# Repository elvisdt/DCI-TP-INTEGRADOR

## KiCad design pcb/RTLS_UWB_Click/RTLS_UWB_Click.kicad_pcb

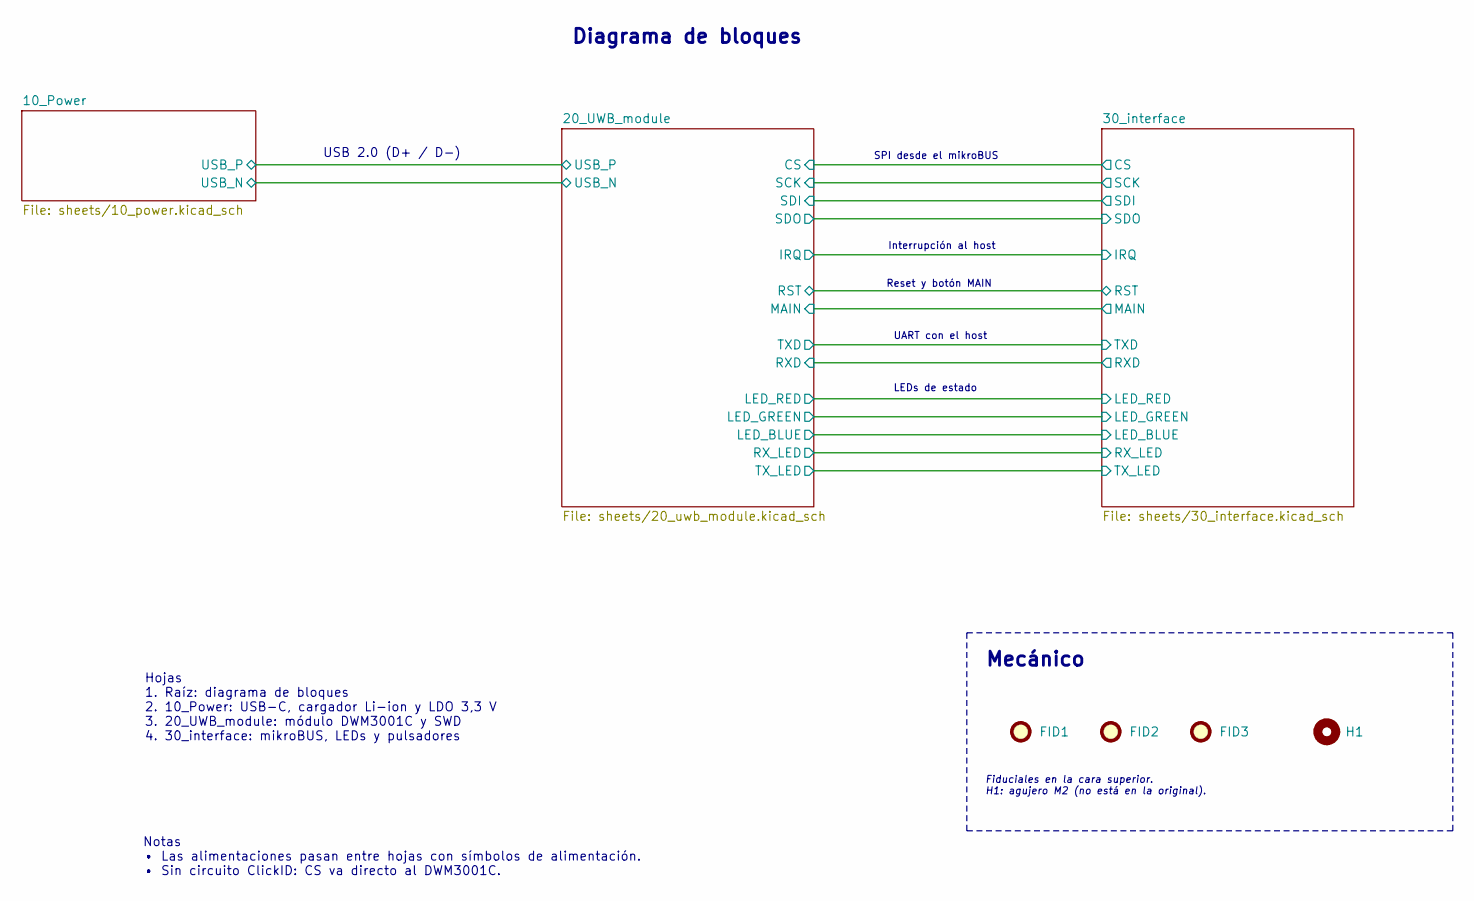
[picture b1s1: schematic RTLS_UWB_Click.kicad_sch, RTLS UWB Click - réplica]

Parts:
FID1, FID2, FID3: Fiducial; Fiducial_1mm_Mask2mm
H1: MountingHole; MountingHole_2.2mm_M2

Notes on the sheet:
UART con el host
Notas • Las alimentaciones pasan entre hojas con símbolos de alimentación. • Sin circuito ClickID: CS va directo al DWM3001C.
Reset y botón MAIN
LEDs de estado
SPI desde el mikroBUS
Interrupción al host
USB 2.0 (D+ / D−)
Fiduciales en la cara superior. H1: agujero M2 (no está en la original).
Hojas 1. Raíz: diagrama de bloques 2. 10_Power: USB-C, cargador Li-ion y LDO 3,3 V 3. 20_UWB_module: módulo DWM3001C y SWD 4. 30_interface: mikroBUS, LEDs y pulsadores
Mecánico
Diagrama de bloques

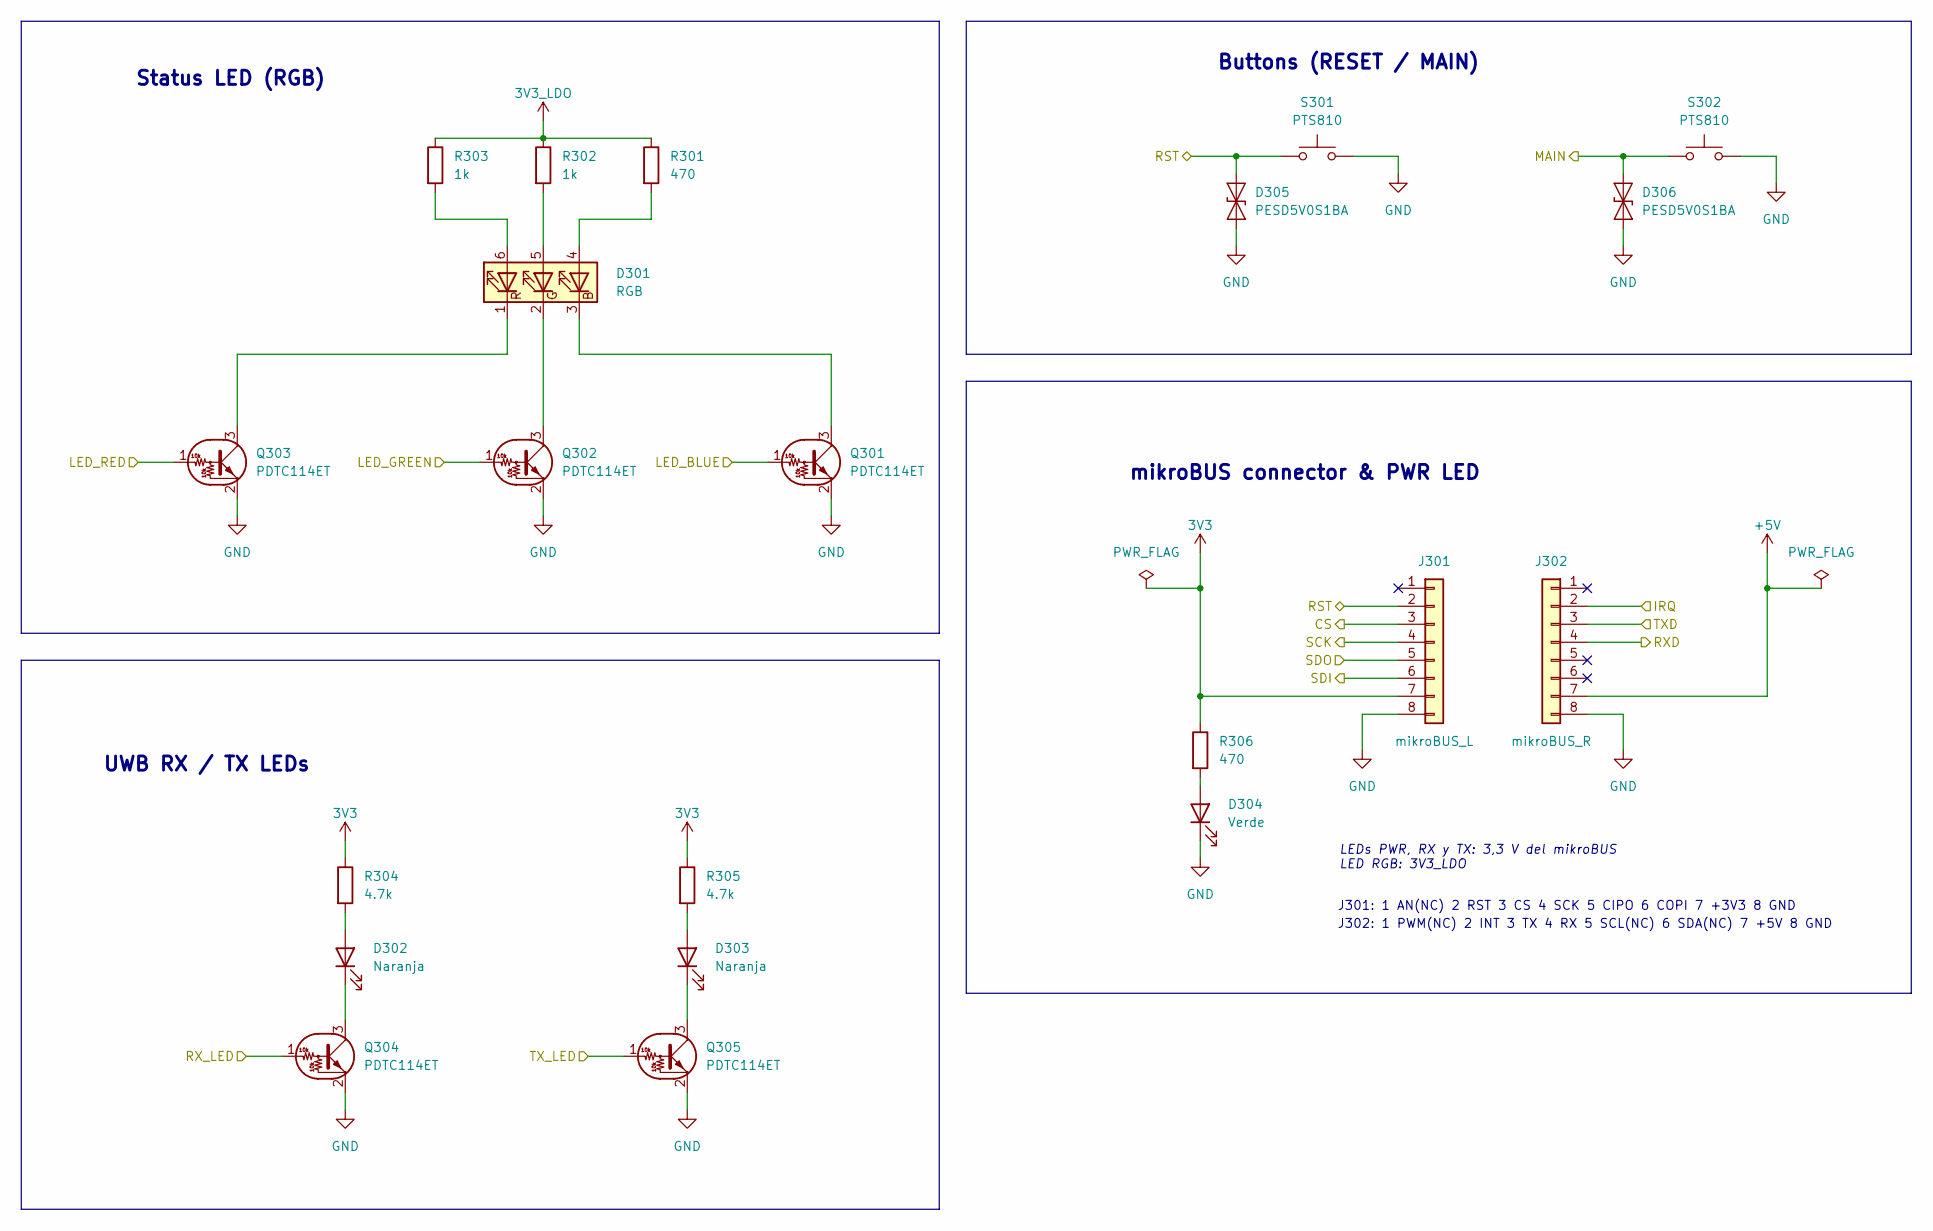
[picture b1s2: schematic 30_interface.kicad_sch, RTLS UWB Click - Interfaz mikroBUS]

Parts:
D301: RGB; LED_RGB_PLCC-6; Digikey# 516-3132-1-ND
D302, D303: Naranja; LED_0805_2012Metric; Digikey# 160-1425-1-ND
D304: Verde; LED_0805_2012Metric; Digikey# 160-1426-1-ND
D305, D306: PESD5V0S1BA; D_SOD-323; Digikey# 1727-PESD5V0S1BA,115CT-ND
J301: mikroBUS_L; PinHeader_1x08_P2.54mm_Vertical; Digikey# 732-5321-ND
J302: mikroBUS_R; PinHeader_1x08_P2.54mm_Vertical; Digikey# 732-5321-ND
Q301, Q302, Q303, Q304, Q305: PDTC114ET; SOT-23; Digikey# 1727-5131-1-ND
R301, R306: 470; R_0805_2012Metric; Digikey# 311-470CRCT-ND
R302, R303: 1k; R_0805_2012Metric; Digikey# 311-1.00KCRCT-ND
R304, R305: 4.7k; R_0805_2012Metric; Digikey# 311-4.70KCRCT-ND
S301, S302: PTS810; SW_SPST_PTS810; Digikey# CKN10504CT-ND

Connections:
3V3: J301.7, R304.1, R305.1, R306.1
3V3_LDO: R301.1, R302.1, R303.1; also elsewhere on the board
+5V: J302.7; also elsewhere on the board
/20_UWB_module/CS: J301.3; also elsewhere on the board
/20_UWB_module/IRQ: J302.2; also elsewhere on the board
/20_UWB_module/LED_BLUE: Q301.1 (B); also elsewhere on the board
/20_UWB_module/LED_GREEN: Q302.1 (B); also elsewhere on the board
/20_UWB_module/LED_RED: Q303.1 (B); also elsewhere on the board
/20_UWB_module/MAIN: D306.2 (A2), S302.1; also elsewhere on the board
/20_UWB_module/RST: D305.2 (A2), J301.2, S301.1; also elsewhere on the board
/20_UWB_module/RXD: J302.4; also elsewhere on the board
/20_UWB_module/RX_LED: Q304.1 (B); also elsewhere on the board
/20_UWB_module/SCK: J301.4; also elsewhere on the board
/20_UWB_module/SDI: J301.6; also elsewhere on the board
/20_UWB_module/SDO: J301.5; also elsewhere on the board
/20_UWB_module/TXD: J302.3; also elsewhere on the board
/20_UWB_module/TX_LED: Q305.1 (B); also elsewhere on the board
GND: D304.1 (K), D305.1 (A1), D306.1 (A1), J301.8, J302.8, Q301.2 (E), Q302.2 (E), Q303.2 (E), Q304.2 (E), Q305.2 (E), S301.2, S302.2; also elsewhere on the board
unnamed: D301.4 (BA), R301.2
unnamed: D301.3 (BK), Q301.3 (C)
unnamed: D301.5 (GA), R302.2
unnamed: D301.2 (GK), Q302.3 (C)
unnamed: D301.6 (RA), R303.2
unnamed: D301.1 (RK), Q303.3 (C)
unnamed: D302.2 (A), R304.2
unnamed: D302.1 (K), Q304.3 (C)
unnamed: D303.2 (A), R305.2
unnamed: D303.1 (K), Q305.3 (C)
unnamed: D304.2 (A), R306.2

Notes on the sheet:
J301: 1 AN(NC) 2 RST 3 CS 4 SCK 5 CIPO 6 COPI 7 +3V3 8 GND
mikroBUS connector & PWR LED
J302: 1 PWM(NC) 2 INT 3 TX 4 RX 5 SCL(NC) 6 SDA(NC) 7 +5V 8 GND
Buttons (RESET / MAIN)
UWB RX / TX LEDs
LEDs PWR, RX y TX: 3,3 V del mikroBUS LED RGB: 3V3_LDO
Status LED (RGB)

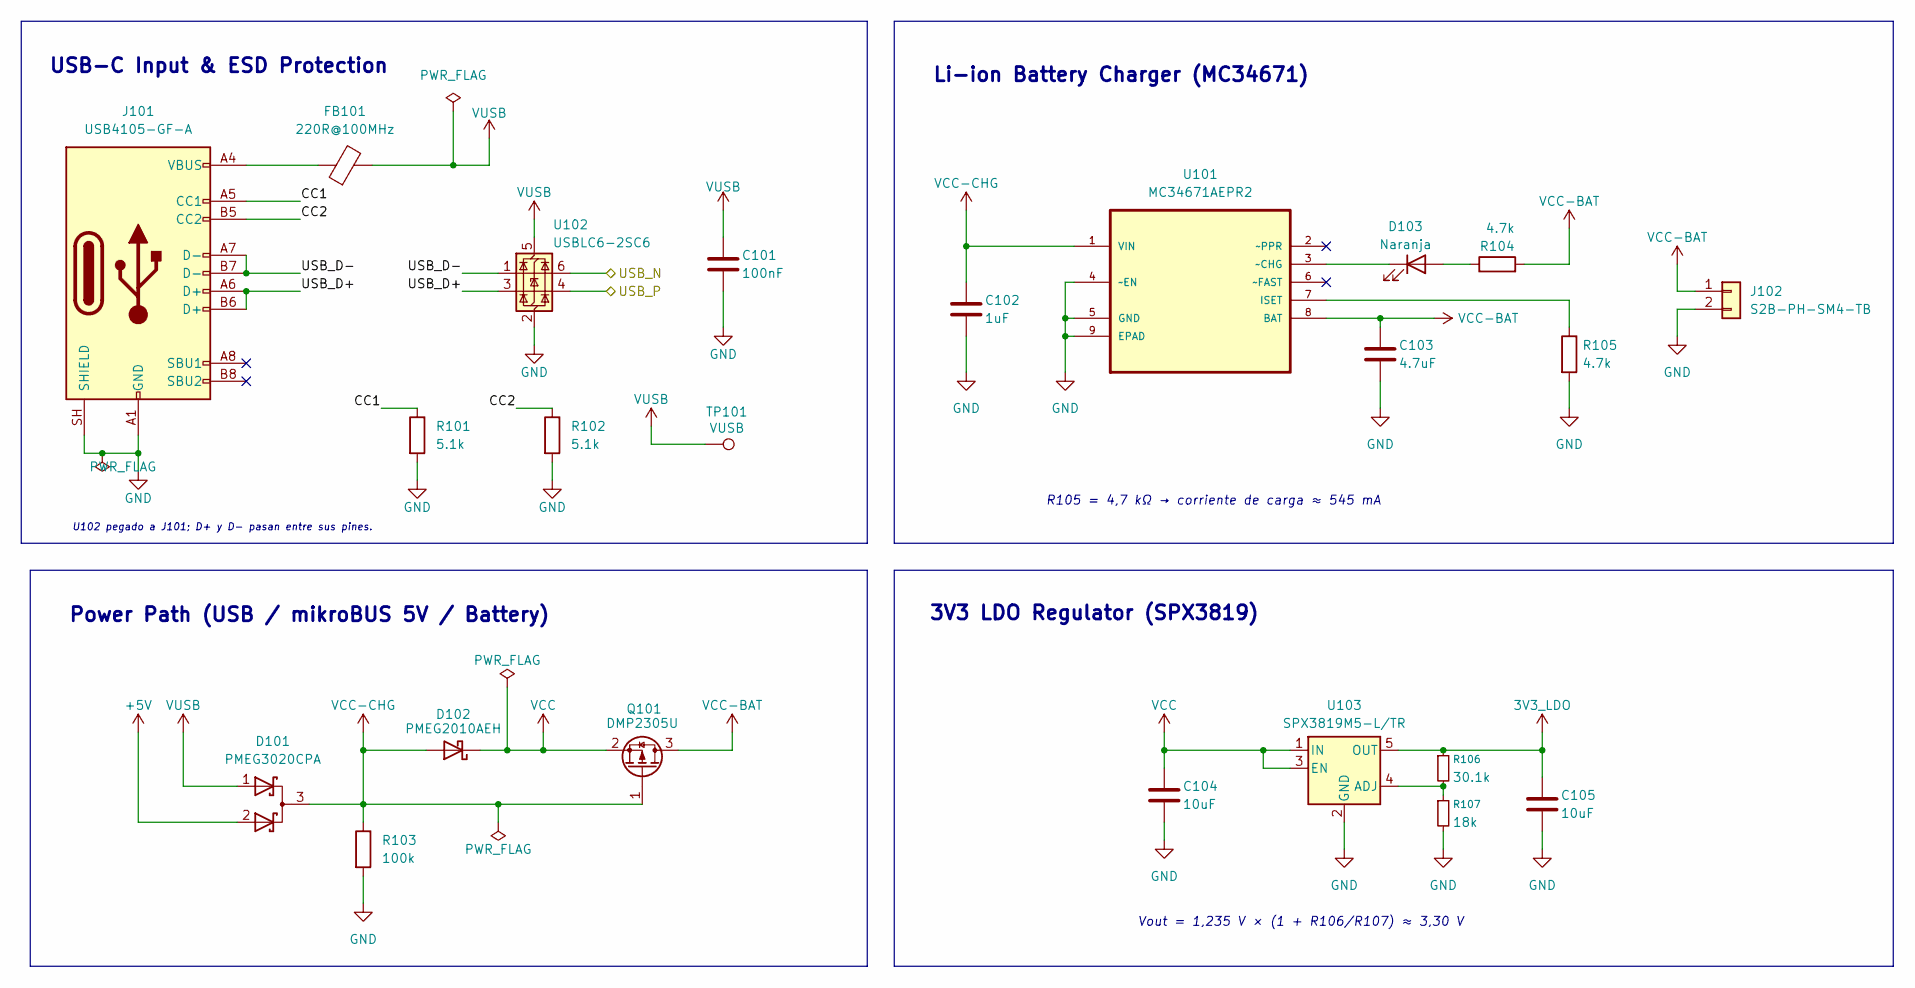
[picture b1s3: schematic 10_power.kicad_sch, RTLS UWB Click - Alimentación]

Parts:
C101: 100nF; C_0805_2012Metric; Digikey# 1276-1003-1-ND
C102: 1uF; C_0805_2012Metric; Digikey# 1276-1066-1-ND
C103: 4.7uF; C_0805_2012Metric; Digikey# 1276-1244-1-ND
C104, C105: 10uF; C_0805_2012Metric; Digikey# 1276-2891-1-ND
D101: PMEG3020CPA; HUSON-3-1EP_2x2mm_P1.3mm_EP1.1x1.6mm; Digikey# 1727-5205-1-ND
D102: PMEG2010AEH; D_SOD-123F; Digikey# 1727-3856-1-ND
D103: Naranja; LED_0805_2012Metric; Digikey# 160-1425-1-ND
FB101: 220R@100MHz; L_0805_2012Metric; Digikey# 490-1054-1-ND
J101: USB4105-GF-A; USB_C_Receptacle_GCT_USB4105-xx-A_16P_TopMnt_Horizontal; Digikey# 2073-USB4105-GF-ACT-ND
J102: S2B-PH-SM4-TB; JST_PH_S2B-PH-SM4-TB_1x02-1MP_P2.00mm_Horizontal; Digikey# 455-S2B-PH-SM4-TBCT-ND
Q101: DMP2305U; SOT-23; Digikey# DMP2305UDICT-ND
R101, R102: 5.1k; R_0805_2012Metric; Digikey# 311-5.10KCRCT-ND
R103: 100k; R_0805_2012Metric; Digikey# 311-100KCRCT-ND
R104, R105: 4.7k; R_0805_2012Metric; Digikey# 311-4.70KCRCT-ND
R106: 30.1k; R_0805_2012Metric; Digikey# 311-30.1KCRCT-ND
R107: 18k; R_0805_2012Metric; Digikey# 311-18.0KCRCT-ND
TP101: VUSB; TestPoint_Pad_D1.5mm
U101: MC34671AEPR2; DFN200X300X65-9N; Digikey# MC34671AEPR2CT-ND
U102: USBLC6-2SC6; SOT-23-6; Digikey# 497-5235-1-ND
U103: SPX3819M5-L/TR; SOT-23-5; Digikey# 1016-1871-1-ND

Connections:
3V3_LDO: C105.1, R106.1, U103.5 (OUT); also elsewhere on the board
+5V: D101.2 (A); also elsewhere on the board
/10_Power/CC1: J101.A5 (CC1), R101.1
/10_Power/CC2: J101.B5 (CC2), R102.1
/10_Power/USB_D+: J101.A6 (D+), J101.B6 (D+), U102.3 (I/O2)
/10_Power/USB_D-: J101.A7 (D-), J101.B7 (D-), U102.1 (I/O1)
/10_Power/USB_N: U102.6 (I/O1); also elsewhere on the board
/10_Power/USB_P: U102.4 (I/O2); also elsewhere on the board
GND: C101.2, C102.2, C103.2, C104.2, C105.2, J101.A1 (GND), J101.A12 (GND), J101.B1 (GND), J101.B12 (GND), J101.SH (SHIELD), J102.2, R101.2, R102.2, R103.2, R105.2, R107.2, U101.4 (~EN), U101.5 (GND), U101.9 (EPAD), U102.2 (GND), U103.2 (GND); also elsewhere on the board
unnamed: D103.2 (A), R104.1
unnamed: D103.1 (K), U101.3 (~CHG)
unnamed: FB101.1, J101.A4 (VBUS), J101.A9 (VBUS), J101.B4 (VBUS), J101.B9 (VBUS)
unnamed: R105.1, U101.7 (ISET)
unnamed: R106.2, R107.1, U103.4 (ADJ)
VCC: C104.1, D102.1 (K), Q101.2 (S), U103.1 (IN), U103.3 (EN)
VCC-BAT: C103.1, J102.1, Q101.3 (D), R104.2, U101.8 (BAT)
VCC-CHG: C102.1, D101.3 (K), D102.2 (A), Q101.1 (G), R103.1, U101.1 (VIN)
VUSB: C101.1, D101.1 (A), FB101.2, TP101.1 (1_1), U102.5 (VBUS); also elsewhere on the board

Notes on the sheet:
Vout = 1,235 V × (1 + R106/R107) ≈ 3,30 V
3V3 LDO Regulator (SPX3819)
U102 pegado a J101; D+ y D− pasan entre sus pines.
USB-C Input & ESD Protection
R105 = 4,7 kΩ → corriente de carga ≈ 545 mA
Power Path (USB / mikroBUS 5V / Battery)
Li-ion Battery Charger (MC34671)

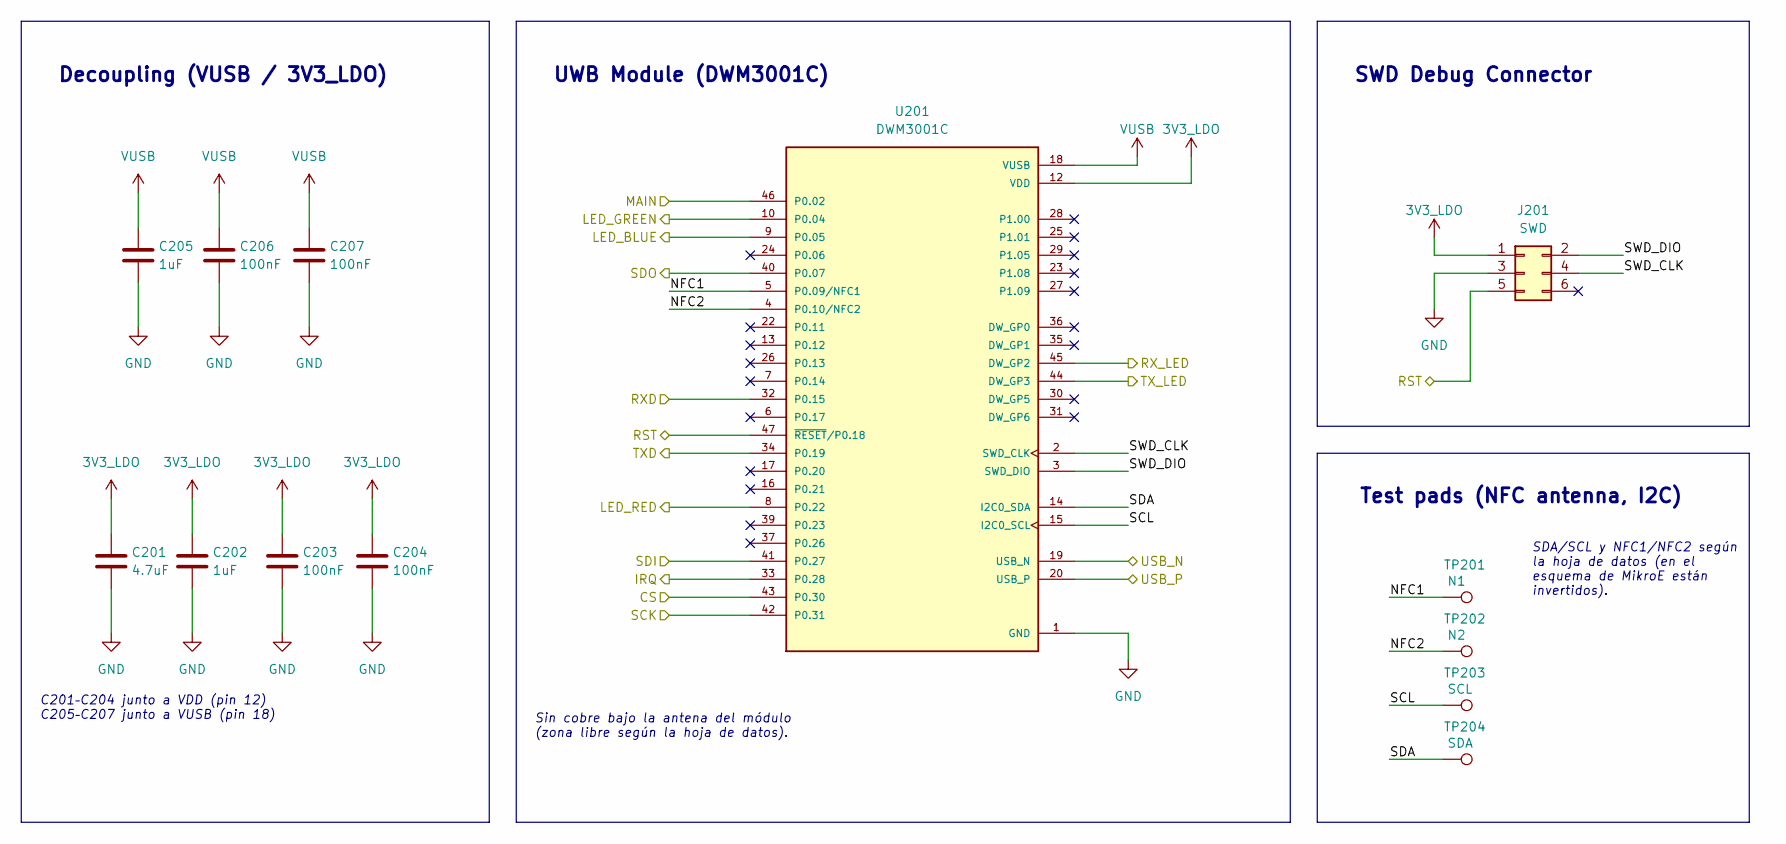
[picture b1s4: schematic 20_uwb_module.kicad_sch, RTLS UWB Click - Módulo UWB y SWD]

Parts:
C201: 4.7uF; C_0805_2012Metric; Digikey# 1276-1244-1-ND
C202, C205: 1uF; C_0805_2012Metric; Digikey# 1276-1066-1-ND
C203, C204, C206, C207: 100nF; C_0805_2012Metric; Digikey# 1276-1003-1-ND
J201: SWD; PinHeader_2x03_P1.27mm_Vertical; Digikey# SAM11230-ND
TP201: N1; TestPoint_Pad_D1.5mm
TP202: N2; TestPoint_Pad_D1.5mm
TP203: SCL; TestPoint_Pad_D1.5mm
TP204: SDA; TestPoint_Pad_D1.5mm
U201: DWM3001C; XCVR_DWM3001C; Digikey# 2312-DWM3001CTR13CT-ND

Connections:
3V3_LDO: C201.1, C202.1, C203.1, C204.1, J201.1, U201.12 (VDD); also elsewhere on the board
/10_Power/USB_N: U201.19 (USB_N); also elsewhere on the board
/10_Power/USB_P: U201.20 (USB_P); also elsewhere on the board
/20_UWB_module/CS: U201.43 (P0.30); also elsewhere on the board
/20_UWB_module/IRQ: U201.33 (P0.28); also elsewhere on the board
/20_UWB_module/LED_BLUE: U201.9 (P0.05); also elsewhere on the board
/20_UWB_module/LED_GREEN: U201.10 (P0.04); also elsewhere on the board
/20_UWB_module/LED_RED: U201.8 (P0.22); also elsewhere on the board
/20_UWB_module/MAIN: U201.46 (P0.02); also elsewhere on the board
/20_UWB_module/NFC1: TP201.1 (1_1), U201.5 (P0.09/NFC1)
/20_UWB_module/NFC2: TP202.1 (1_1), U201.4 (P0.10/NFC2)
/20_UWB_module/RST: J201.5, U201.47 (~RESET/P0.18); also elsewhere on the board
/20_UWB_module/RXD: U201.32 (P0.15); also elsewhere on the board
/20_UWB_module/RX_LED: U201.45 (DW_GP2); also elsewhere on the board
/20_UWB_module/SCK: U201.42 (P0.31); also elsewhere on the board
/20_UWB_module/SCL: TP203.1 (1_1), U201.15 (I2C0_SCL)
/20_UWB_module/SDA: TP204.1 (1_1), U201.14 (I2C0_SDA)
/20_UWB_module/SDI: U201.41 (P0.27); also elsewhere on the board
/20_UWB_module/SDO: U201.40 (P0.07); also elsewhere on the board
/20_UWB_module/SWD_CLK: J201.4, U201.2 (SWD_CLK)
/20_UWB_module/SWD_DIO: J201.2, U201.3 (SWD_DIO)
/20_UWB_module/TXD: U201.34 (P0.19); also elsewhere on the board
/20_UWB_module/TX_LED: U201.44 (DW_GP3); also elsewhere on the board
GND: C201.2, C202.2, C203.2, C204.2, C205.2, C206.2, C207.2, J201.3, U201.1 (GND), U201.11 (GND), U201.21 (GND), U201.38 (GND), U201.48 (GND); also elsewhere on the board
VUSB: C205.1, C206.1, C207.1, U201.18 (VUSB); also elsewhere on the board

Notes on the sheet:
Sin cobre bajo la antena del módulo (zona libre según la hoja de datos).
Decoupling (VUSB / 3V3_LDO)
Test pads (NFC antenna, I2C)
SDA/SCL y NFC1/NFC2 según la hoja de datos (en el esquema de MikroE están invertidos).
C201–C204 junto a VDD (pin 12) C205–C207 junto a VUSB (pin 18)
SWD Debug Connector
UWB Module (DWM3001C)

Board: 2 copper layers, 61 parts (0 on the bottom side), 50 nets, no tracks yet.

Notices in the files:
pcb/RTLS_UWB_Click/RTLS_UWB_Click.kicad_sch:
Licencia: CERN-OHL-S-2.0
